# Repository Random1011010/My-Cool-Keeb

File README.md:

# My-Cool-Keeb
# Name: Morning Star

**Morning Star** is a custom 81-key mechanical keyboard powered by the **Hack Club Orpheus Pico** (RP2040). Built with dual rotary encoders, ultra-quiet linear switches, and a custom 2-layer PCB inside a 3D-printed enclosure, it delivers a high-functionality, low-noise typing experience.

---

## 🛠️ Project Writeup

### What I Built
Morning Star is a custom-designed, 81-key mechanical keyboard featuring a dedicated function row, arrow cluster, and dual EC11 rotary encoders. 

* **Microcontroller**: Powered by the Hack Club Orpheus Pico (RP2040).
* **Sound Profile**: Engineered for silent operation using Outemu Silent White linear switches, blank MOA profile PBT keycaps, and pre-clipped Chosfox V3 plate-mount stabilizers.
* **PCB & Hardware**: Custom 2-layer PCB designed, housed in a 3D-printed enclosure held together with M3 brass heat-set inserts and stainless steel hex socket screws.

---

### Why I Built It
Standard off-the-shelf mechanical keyboards are often either too noisy for shared environments or lack the physical control density needed for media editing, live sound workflows, and rapid navigation. 

I wanted to design a custom board from scratch that solved these problems:
1. **Dual Encoder Control**: Placing two tactile knobs directly on the layout gives instant physical control over volume, timeline scrubbing, and macro adjustments without leaving the home row.
2. **Silent Treatment**: By choosing silent white linear switches and plate-mounted stabilizers with pre-clipped stems, I wanted to eliminate rattle and any noise (I study at night so I would get in trouble if it was loud).

---

### What I Learned
Building Morning Star involved learning hardware production, PCB fabrication constraints, and firmware matrix logic:

* **PCB Manufacturing & Cost Optimization**: I learned how small design decisions directly impact manufacturing price. By selecting "Tented" via covering, I eliminated extra processing surcharges on JLCPCB while keeping standard matrix routing intact.
* **Hardware Sourcing & Budgeting**: Balancing component lead times and shipping fees taught me how to structure a realistic Bill of Materials across multiple suppliers (AliExpress, Amazon, JLCPCB) while staying strictly within budget limits.
* **Mechanical Design & Fasteners**: I learned why direct-threading screws into 3D-printed plastic leads to stripped threads over time, and how using a soldering iron to melt brass heat-set inserts into internal bosses provides strong, long-lasting metal threads for continuous teardowns.
* **Matrix Logic & Firmware**: I gained experience configuring diode-isolated key matrices (1N4148 diodes) to ensure full N-Key Rollover (NKRO) without ghosting, as well as mapping quadrature encoder signals to GPIO pins on the RP2040.

---

## 📋 Bill of Materials (BOM)

| Part Description | Qty | Unit Cost (USD) | Total Cost (USD) | Source / Link |
| :--- | :---: | :---: | :---: | :--- |
| **Orpheus Pico Microcontroller** | 1 | $0.00 | $0.00 | [Hack Club GitHub](https://github.com/hackclub/orpheus-pico) |
| **Outemu Silent White Linear Switches** (90 pcs) | 90 | $0.27 | $23.90 | [AliExpress](https://www.aliexpress.com/item/1005002378701948.html) |
| **132-Key White Blank MOA Profile Keycaps** | 1 | $20.96 | $20.96 | [AliExpress](https://www.aliexpress.com/) |
| **1N4148 Signal Diodes** (100-pack) | 100 | $0.016 | $1.64 | [AliExpress](https://www.aliexpress.com/item/1005002339916163.html) |
| **EC11 20mm Rotary Encoders** (2-pack) | 1 | $3.50 | $3.50 | [AliExpress](https://www.aliexpress.com/) |
| **M3 x 20mm Stainless Steel Screws** (100-pack) | 100 | $0.052 | $5.22 | [AliExpress](https://www.aliexpress.com/) |
| **HANGLIFE M3 Brass Heat-Set Inserts** (100-pack) | 100 | $0.057 | $5.66 | [Amazon Canada](https://www.amazon.ca/) |
| **Chosfox V3 Plate Mount Stabilizers Kit** | 1 | $8.57 | $8.57 | [AliExpress](https://www.aliexpress.com/item/1005007299976098.html) |
| **Custom 2-Layer PCB Fabrication** (5 pcs total) | 1 | $58.85 | $58.85 | [JLCPCB](https://jlcpcb.com/) |
| **Total Estimated Cost** | | | **~$128.30 USD** | |

---

## 🛠️ Hardware Specifications

* **MCU**: Hack Club Orpheus Pico (RP2040)
* **Matrix Architecture**
* **Encoders**: 2x EC11 5-pin encoders connected to dedicated GPIO channels.
* **Enclosure Fasteners**: M3 x D5 x L4 mm brass heat-set inserts with M3 x 20mm.
* **Stabilizers**: Chosfox V3 plate-mount stabilizers for keycaps ≥ 2u.

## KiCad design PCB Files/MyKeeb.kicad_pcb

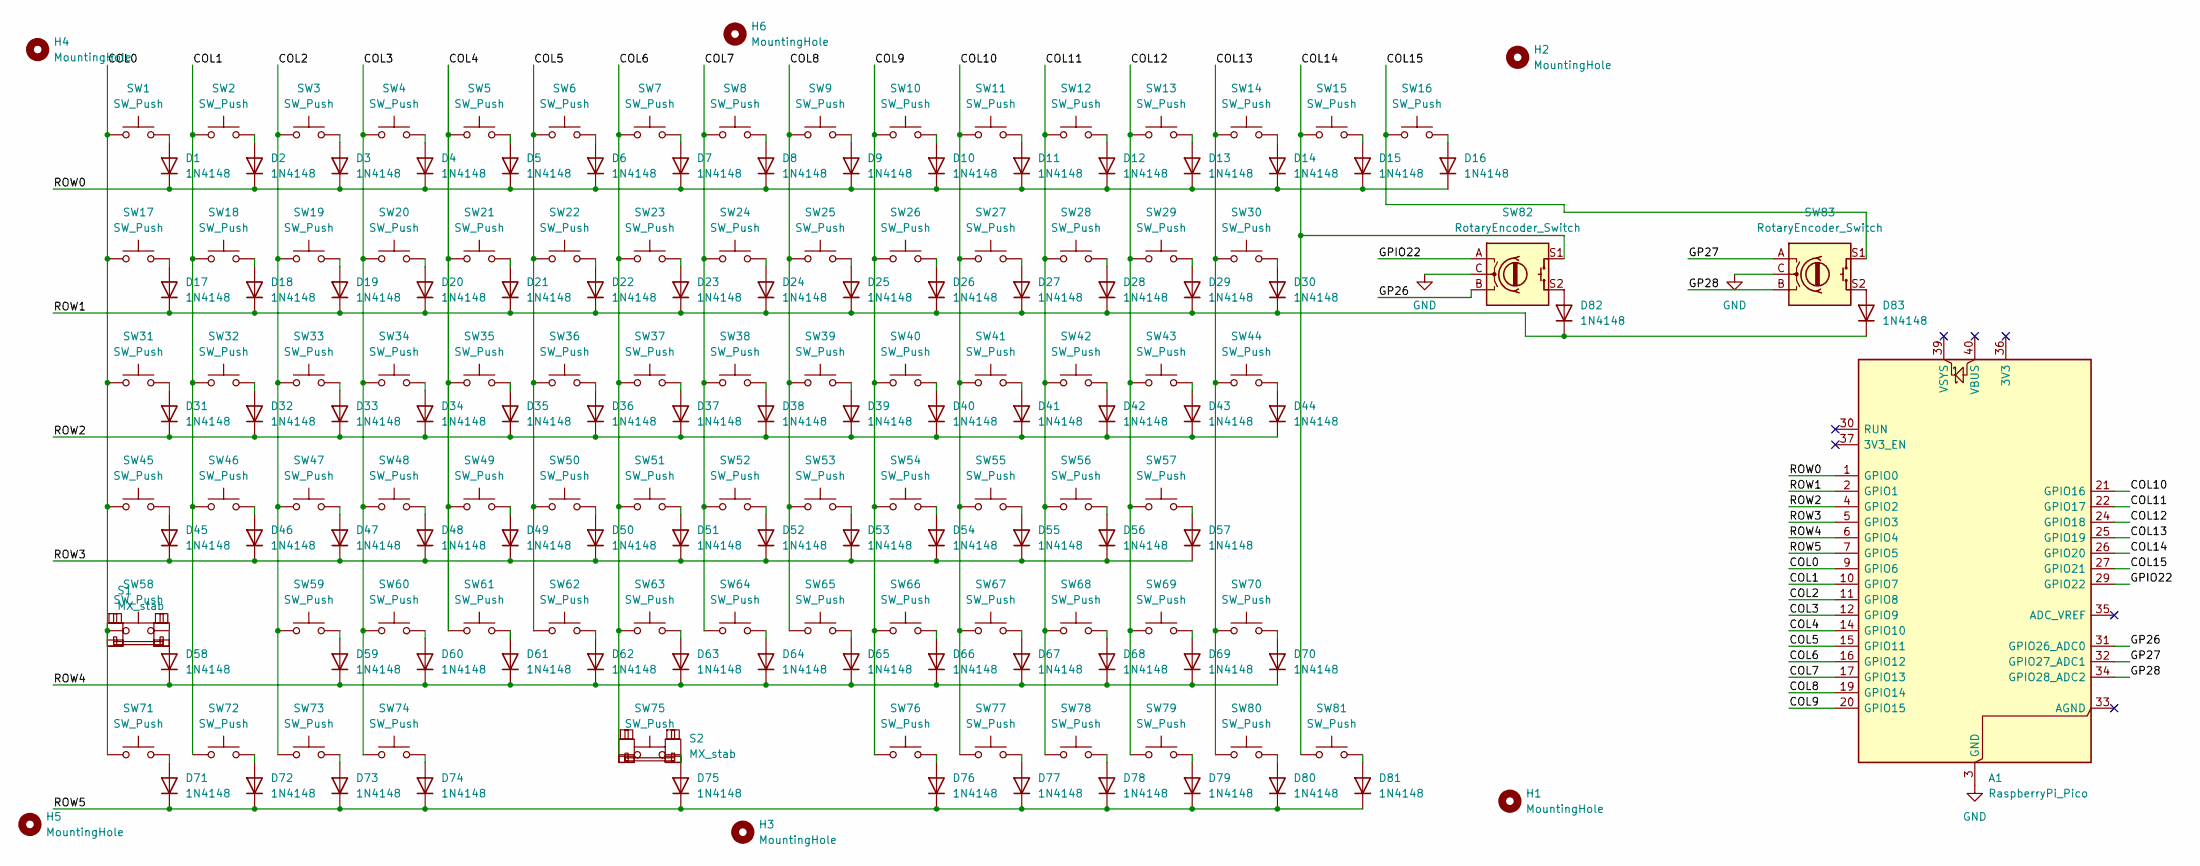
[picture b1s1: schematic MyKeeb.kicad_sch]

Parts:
A1: RaspberryPi_Pico; RaspberryPi_Pico_Common_THT
D1, D2, D3, D4, D5, D6, D7, D8, D9, D10, D11, D12, D13, D14, D15, D16, D17, D18, D19, D20, D21, D22, D23, D24, D25, D26, D27, D28, D29, D30, D31, D32, D33, D34, D35, D36, D37, D38, D39, D40, D41, D42, D43, D44, D45, D46, D47, D48, D49, D50, D51, D52, D53, D54, D55, D56, D57, D58, D59, D60, D61, D62, D63, D64, D65, D66, D67, D68, D69, D70, D71, D72, D73, D74, D75, D76, D77, D78, D79, D80, D81, D82, D83: 1N4148; D_DO-35_SOD27_P7.62mm_Horizontal
H1, H2, H3, H4, H5, H6: MountingHole; MountingHole_3.2mm_M3
S1: MX_stab; STAB_MX_P_2.25u
S2: MX_stab; STAB_MX_P_5u
SW1, SW30, SW31: SW_Push; SW_MX_1.5u
SW2, SW3, SW4, SW5, SW6, SW7, SW8, SW9, SW10, SW11, SW12, SW13, SW14, SW15, SW16, SW17, SW18, SW19, SW20, SW21, SW22, SW23, SW24, SW25, SW26, SW27, SW28, SW29, SW32, SW33, SW34, SW35, SW36, SW37, SW38, SW39, SW40, SW41, SW42, SW43, SW44, SW46, SW47, SW48, SW49, SW50, SW51, SW52, SW53, SW54, SW55, SW56, SW58, SW59, SW60, SW61, SW62, SW63, SW64, SW65, SW66, SW67, SW68, SW70, SW71, SW72, SW73, SW75, SW77, SW78, SW79, SW80, SW81: SW_Push; SW_MX_1u
SW45, SW57: SW_Push; SW_MX_1.75u
SW69, SW74, SW76: SW_Push; SW_MX_1.25u
SW82, SW83: RotaryEncoder_Switch; ROT_Alps_EC11E-Switch

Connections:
/COL0: A1.9 (GPIO6), SW1.1, SW17.1, SW31.1, SW45.1, SW58.1, SW71.1
/COL1: A1.10 (GPIO7), SW2.1, SW18.1, SW32.1, SW46.1, SW72.1
/COL2: A1.11 (GPIO8), SW3.1, SW19.1, SW33.1, SW47.1, SW59.1, SW73.1
/COL3: A1.12 (GPIO9), SW4.1, SW20.1, SW34.1, SW48.1, SW60.1, SW74.1
/COL4: A1.14 (GPIO10), SW5.1, SW21.1, SW35.1, SW49.1, SW61.1
/COL5: A1.15 (GPIO11), SW6.1, SW22.1, SW36.1, SW50.1, SW62.1
/COL6: A1.16 (GPIO12), SW7.1, SW23.1, SW37.1, SW51.1, SW63.1, SW75.1
/COL7: A1.17 (GPIO13), SW8.1, SW24.1, SW38.1, SW52.1, SW64.1
/COL8: A1.19 (GPIO14), SW9.1, SW25.1, SW39.1, SW53.1, SW65.1
/COL9: A1.20 (GPIO15), SW10.1, SW26.1, SW40.1, SW54.1, SW66.1, SW76.1
/COL10: A1.21 (GPIO16), SW11.1, SW27.1, SW41.1, SW55.1, SW67.1, SW77.1
/COL11: A1.22 (GPIO17), SW12.1, SW28.1, SW42.1, SW56.1, SW68.1, SW78.1
/COL12: A1.24 (GPIO18), SW13.1, SW29.1, SW43.1, SW57.1, SW69.1, SW79.1
/COL13: A1.25 (GPIO19), SW14.1, SW30.1, SW44.1, SW70.1, SW80.1
/COL14: A1.26 (GPIO20), SW15.1, SW81.1, SW82.S1
/COL15: A1.27 (GPIO21), SW16.1, SW83.S1
/GP26: A1.31 (GPIO26_ADC0), SW82.B
/GP27: A1.32 (GPIO27_ADC1), SW83.A
/GP28: A1.34 (GPIO28_ADC2), SW83.B
/GPIO22: A1.29 (GPIO22), SW82.A
/ROW0: A1.1 (GPIO0), D1.1 (K), D2.1 (K), D3.1 (K), D4.1 (K), D5.1 (K), D6.1 (K), D7.1 (K), D8.1 (K), D9.1 (K), D10.1 (K), D11.1 (K), D12.1 (K), D13.1 (K), D14.1 (K), D15.1 (K), D16.1 (K)
/ROW1: A1.2 (GPIO1), D17.1 (K), D18.1 (K), D19.1 (K), D20.1 (K), D21.1 (K), D22.1 (K), D23.1 (K), D24.1 (K), D25.1 (K), D26.1 (K), D27.1 (K), D28.1 (K), D29.1 (K), D30.1 (K), D82.1 (K), D83.1 (K)
/ROW2: A1.4 (GPIO2), D31.1 (K), D32.1 (K), D33.1 (K), D34.1 (K), D35.1 (K), D36.1 (K), D37.1 (K), D38.1 (K), D39.1 (K), D40.1 (K), D41.1 (K), D42.1 (K), D43.1 (K), D44.1 (K)
/ROW3: A1.5 (GPIO3), D45.1 (K), D46.1 (K), D47.1 (K), D48.1 (K), D49.1 (K), D50.1 (K), D51.1 (K), D52.1 (K), D53.1 (K), D54.1 (K), D55.1 (K), D56.1 (K), D57.1 (K)
/ROW4: A1.6 (GPIO4), D58.1 (K), D59.1 (K), D60.1 (K), D61.1 (K), D62.1 (K), D63.1 (K), D64.1 (K), D65.1 (K), D66.1 (K), D67.1 (K), D68.1 (K), D69.1 (K), D70.1 (K)
/ROW5: A1.7 (GPIO5), D71.1 (K), D72.1 (K), D73.1 (K), D74.1 (K), D75.1 (K), D76.1 (K), D77.1 (K), D78.1 (K), D79.1 (K), D80.1 (K), D81.1 (K)
GND: A1.3 (GND), A1.8 (GND), A1.13 (GND), A1.18 (GND), A1.23 (GND), A1.28 (GND), A1.38 (GND), SW82.C, SW83.C
unnamed: D1.2 (A), SW1.2
unnamed: D2.2 (A), SW2.2
unnamed: D3.2 (A), SW3.2
unnamed: D4.2 (A), SW4.2
unnamed: D5.2 (A), SW5.2
unnamed: D6.2 (A), SW6.2
unnamed: D7.2 (A), SW7.2
unnamed: D8.2 (A), SW8.2
unnamed: D9.2 (A), SW9.2
unnamed: D10.2 (A), SW10.2
unnamed: D11.2 (A), SW11.2
unnamed: D12.2 (A), SW12.2
unnamed: D13.2 (A), SW13.2
unnamed: D14.2 (A), SW14.2
unnamed: D15.2 (A), SW15.2
unnamed: D16.2 (A), SW16.2
unnamed: D17.2 (A), SW17.2
unnamed: D18.2 (A), SW18.2
unnamed: D19.2 (A), SW19.2
unnamed: D20.2 (A), SW20.2
unnamed: D21.2 (A), SW21.2
unnamed: D22.2 (A), SW22.2
unnamed: D23.2 (A), SW23.2
unnamed: D24.2 (A), SW24.2
unnamed: D25.2 (A), SW25.2
unnamed: D26.2 (A), SW26.2
unnamed: D27.2 (A), SW27.2
unnamed: D28.2 (A), SW28.2
unnamed: D29.2 (A), SW29.2
unnamed: D30.2 (A), SW30.2
unnamed: D31.2 (A), SW31.2
unnamed: D32.2 (A), SW32.2
unnamed: D33.2 (A), SW33.2
unnamed: D34.2 (A), SW34.2
unnamed: D35.2 (A), SW35.2
unnamed: D36.2 (A), SW36.2
unnamed: D37.2 (A), SW37.2
unnamed: D38.2 (A), SW38.2
unnamed: D39.2 (A), SW39.2
unnamed: D40.2 (A), SW40.2
unnamed: D41.2 (A), SW41.2
unnamed: D42.2 (A), SW42.2
unnamed: D43.2 (A), SW43.2
unnamed: D44.2 (A), SW44.2
unnamed: D45.2 (A), SW45.2
unnamed: D46.2 (A), SW46.2
unnamed: D47.2 (A), SW47.2
unnamed: D48.2 (A), SW48.2
unnamed: D49.2 (A), SW49.2
unnamed: D50.2 (A), SW50.2
unnamed: D51.2 (A), SW51.2
unnamed: D52.2 (A), SW52.2
unnamed: D53.2 (A), SW53.2
unnamed: D54.2 (A), SW54.2
unnamed: D55.2 (A), SW55.2
unnamed: D56.2 (A), SW56.2
unnamed: D57.2 (A), SW57.2
unnamed: D58.2 (A), SW58.2
unnamed: D59.2 (A), SW59.2
unnamed: D60.2 (A), SW60.2
unnamed: D61.2 (A), SW61.2
unnamed: D62.2 (A), SW62.2
unnamed: D63.2 (A), SW63.2
unnamed: D64.2 (A), SW64.2
unnamed: D65.2 (A), SW65.2
unnamed: D66.2 (A), SW66.2
unnamed: D67.2 (A), SW67.2
unnamed: D68.2 (A), SW68.2
unnamed: D69.2 (A), SW69.2
unnamed: D70.2 (A), SW70.2
unnamed: D71.2 (A), SW71.2
unnamed: D72.2 (A), SW72.2
unnamed: D73.2 (A), SW73.2
unnamed: D74.2 (A), SW74.2
unnamed: D75.2 (A), SW75.2
unnamed: D76.2 (A), SW76.2
unnamed: D77.2 (A), SW77.2
unnamed: D78.2 (A), SW78.2
unnamed: D79.2 (A), SW79.2
unnamed: D80.2 (A), SW80.2
unnamed: D81.2 (A), SW81.2
unnamed: D82.2 (A), SW82.S2
unnamed: D83.2 (A), SW83.S2

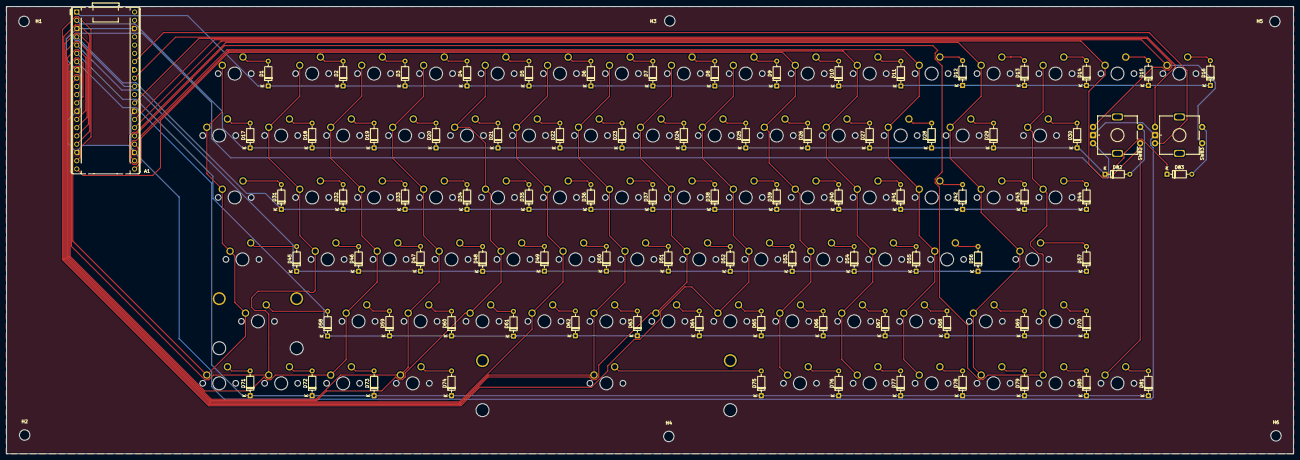
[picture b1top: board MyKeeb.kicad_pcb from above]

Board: 2 copper layers, 395.7 x 137.5 mm, 175 parts (0 on the bottom side), 110 nets.

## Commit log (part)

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2026-06-29 Created PCB Files
2026-06-29 Create Case Files
